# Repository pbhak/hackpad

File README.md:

# Parneel's Hackpad
My Hackpad, designed for IDE functionality and general-purpose stuff \
Designed for [Hackpad](https://hackpad.hackclub.com)

## Screenshots
### PCB

*PCB schematic* \

*PCB* \

*PCB, rendered front side* \

*PCB, rendered back side* \

### Case

*Top view* \

*Side view* \

*Other side view* \

## BOM
| Component                | Qty | Comments                                                                                                                 |
|--------------------------|-----|--------------------------------------------------------------------------------------------------------------------------|
| XIAO RP2040              | 1   |                                                                                                                          |
| EC11 Rotary Encoder      | 1   |                                                                                                                          |
| Cherry MX-style switches | 12  | will be ordering [custom switches](https://divinikey.com/products/gateron-smoothie-linear-switches) w/ grant if possible |
| 1N4148 diodes            | 12  |                                                                                                                          |
| 0.91" SSD1306 OLED       | 1   |                                                                                                                          |
| 1U Keycaps                  | 12  | preferably mostly white with a few red/black ones                                                                        |
| M3x16 screws             | 4   |                                                                                                                          |
| M3 heat-set inserts      | 4   |                                                                                                                          |
| Case.stl                 | 1   | black if possible                                                                                                        |
| Plate.stl                | 1   | black if possible                                                                                                        |
| Knob.stl                 | 1   | black if possible                                                                                                        |
| PCB                      | 1   |

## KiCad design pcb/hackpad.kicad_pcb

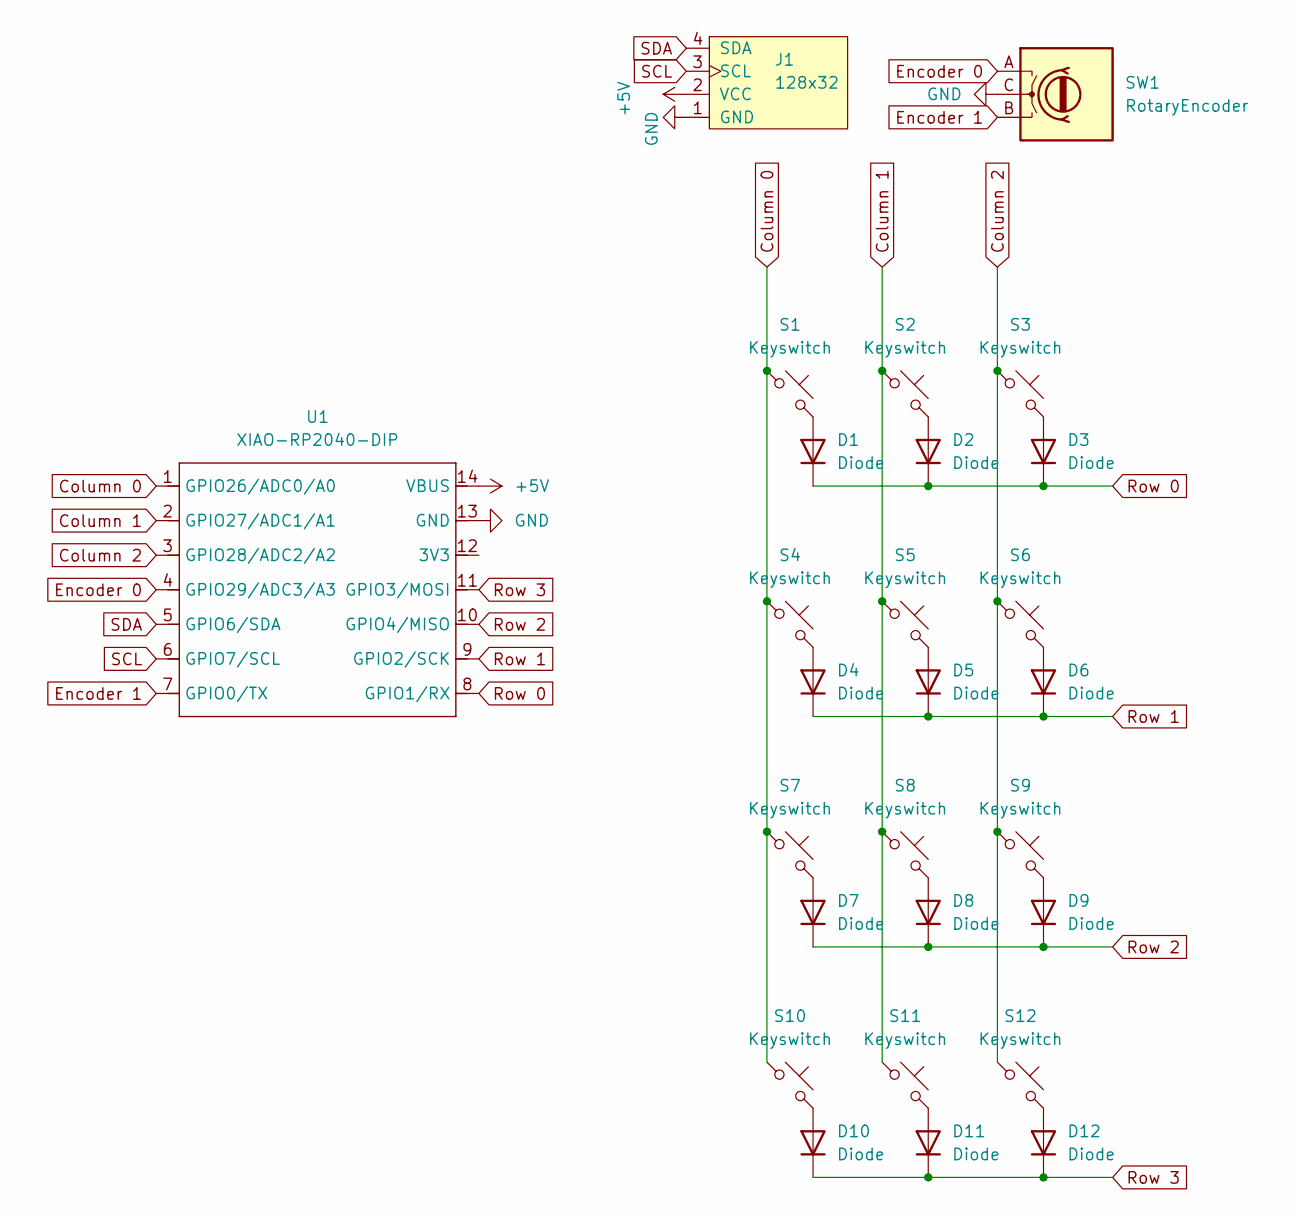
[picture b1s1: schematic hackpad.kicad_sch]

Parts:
D1, D2, D3, D4, D5, D6, D7, D8, D9, D10, D11, D12: Diode; Diode_DO-35
J1: 128x32; OLED_128x32
S1, S2, S3, S4, S5, S6, S7, S8, S9, S10, S11, S12: Keyswitch; MX-Solderable-1U
SW1: RotaryEncoder; RotaryEncoder_Alps_EC11E_Vertical_H20mm_CircularMountingHol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
U1: XIAO-RP2040-DIP

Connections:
+5V: J1.2 (VCC), U1.14 (VBUS)
Column 0: S1.1, S4.1, S7.1, S10.1, U1.1 (GPIO26/ADC0/A0)
Column 1: S2.1, S5.1, S8.1, S11.1, U1.2 (GPIO27/ADC1/A1)
Column 2: S3.1, S6.1, S9.1, S12.1, U1.3 (GPIO28/ADC2/A2)
Encoder 0: SW1.A, U1.4 (GPIO29/ADC3/A3)
Encoder 1: SW1.B, U1.7 (GPIO0/TX)
GND: J1.1 (GND), SW1.C, U1.13 (GND)
unnamed: D1.2 (A), S1.2
unnamed: D2.2 (A), S2.2
unnamed: D3.2 (A), S3.2
unnamed: D4.2 (A), S4.2
unnamed: D5.2 (A), S5.2
unnamed: D6.2 (A), S6.2
unnamed: D7.2 (A), S7.2
unnamed: D8.2 (A), S8.2
unnamed: D9.2 (A), S9.2
unnamed: D10.2 (A), S10.2
unnamed: D11.2 (A), S11.2
unnamed: D12.2 (A), S12.2
Row 0: D1.1 (K), D2.1 (K), D3.1 (K), U1.8 (GPIO1/RX)
Row 1: D4.1 (K), D5.1 (K), D6.1 (K), U1.9 (GPIO2/SCK)
Row 2: D7.1 (K), D8.1 (K), D9.1 (K), U1.10 (GPIO4/MISO)
Row 3: D10.1 (K), D11.1 (K), D12.1 (K), U1.11 (GPIO3/MOSI)
SCL: J1.3 (SCL), U1.6 (GPIO7/SCL)
SDA: J1.4 (SDA), U1.5 (GPIO6/SDA)

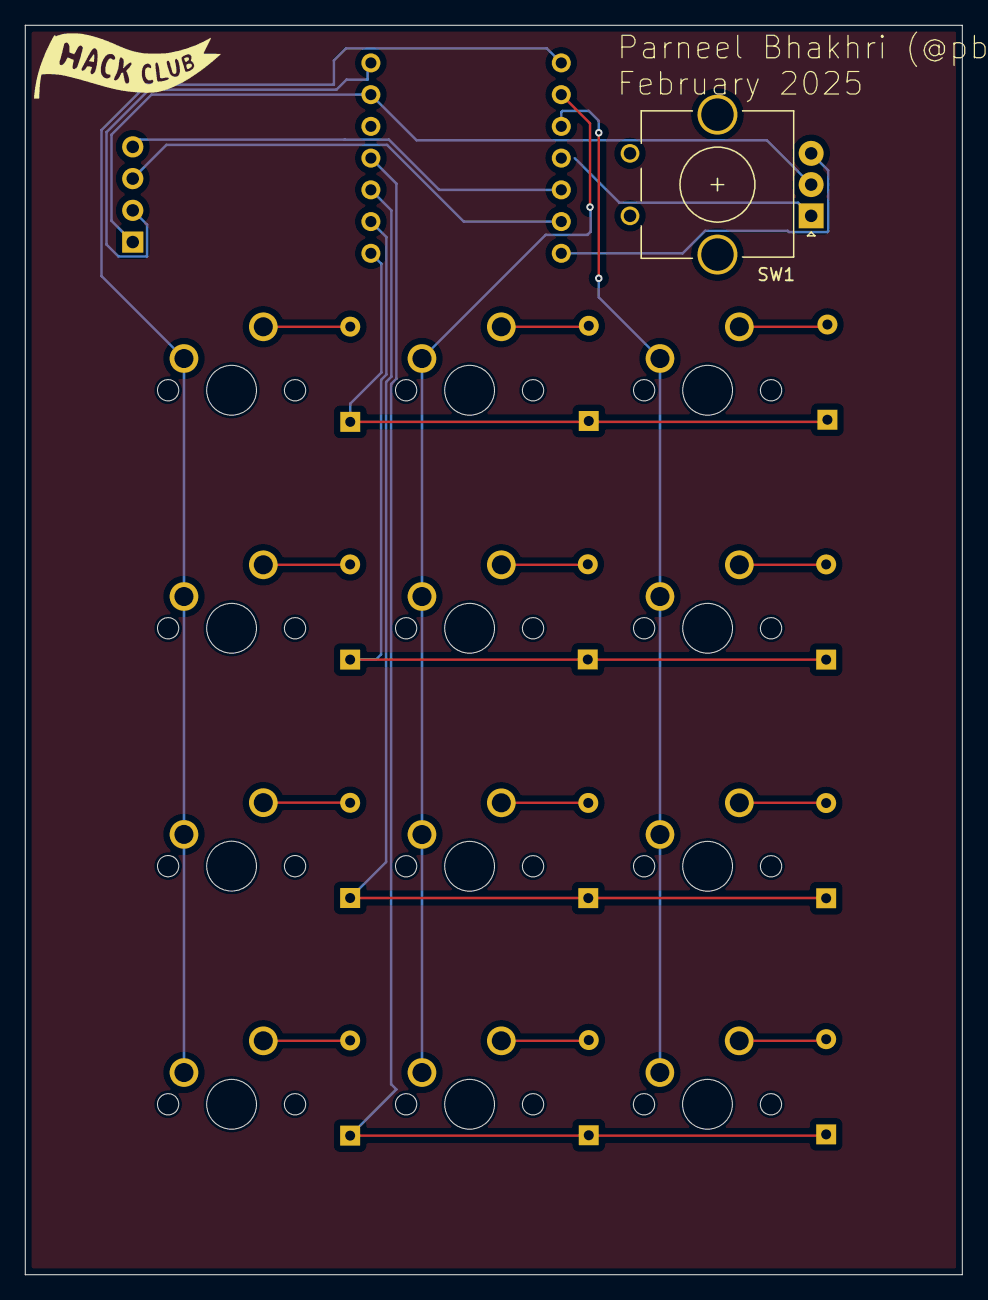
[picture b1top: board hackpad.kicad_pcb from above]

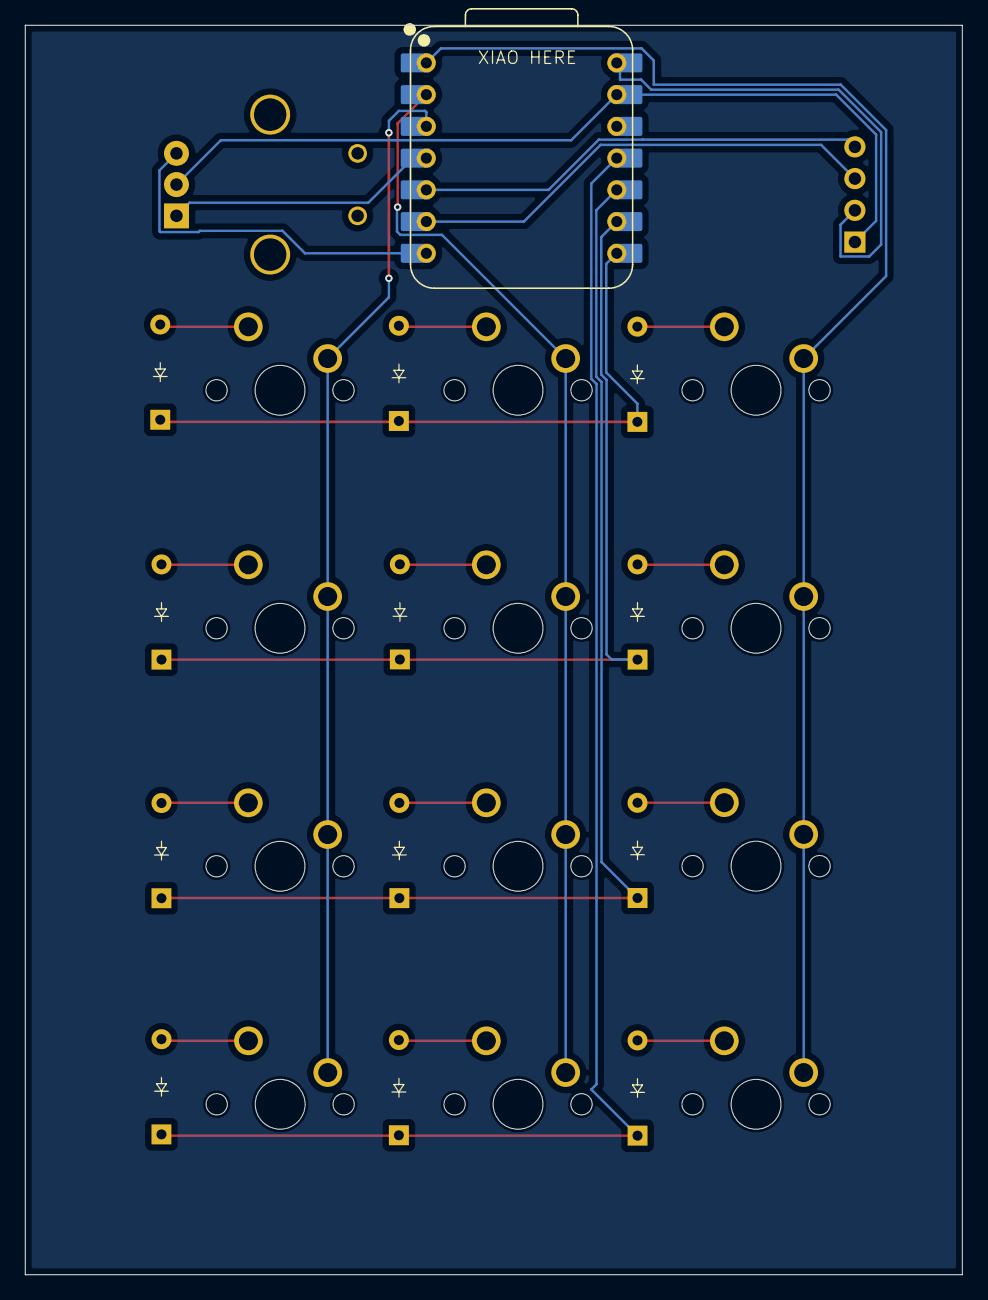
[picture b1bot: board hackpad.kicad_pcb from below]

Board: 2 copper layers, 75.0 x 100.0 mm, 27 parts (13 on the bottom side), 25 nets.

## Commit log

2025-02-14 add pcb
2025-02-14 remove unneeded files from pcb
2025-02-14 add case
2025-02-14 optimize routing
2025-02-18 update readme, make firmware
2025-02-18 add assets and stl files, create bom
2025-02-18 add images and bom
2025-02-18 add 1u
2025-02-19 update images
2025-02-19 change image size
2025-02-19 line break
